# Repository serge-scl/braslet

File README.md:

Here I have collected calculations and drawings of a project for creating a device for removing disposable medical gloves with subsequent storage, accounting and disposal. This procedure is necessary to avoid a significant risk of infection during the work of medical staff. Various visual aids here offer a written and illustrated procedure on how to properly remove a disposable glove to avoid contact with a contaminated surface. However, the human factor suggests that sooner or later a mistake happens. This possibility is exacerbated by the factor of fatigue and stress.
The root directory contains files where I make various calculations. The earliest calculations related to the overall dimensions of the bracelet and its details relative to the size of the coverage of a man's or woman's wrist. These calculations cannot be called accurate. These are just some starting points.
Another group of calculations concerned the ability to determine the forces that a pneumatic mechanism must create for successful operation. This calculation showed that the range can vary quite widely. In the future, using differential equations will allow us to find more optimal values.
And the third type of calculation is the calculation of the solenoid valve that controls the operation of the suction cup. I tried to verify these calculations as far as possible.
The designCAD folder contains drawings in an open format. This work has not yet been completed in its entirety. So far, there are no drawings of the case, the upper and lower parts of the entire device, and it remains to be done. In the upper part there will be a working niche with a bracelet, and receivers and micropumps working with it. At the bottom there will be a negative pressure fan and storage for used gloves. So far, only part of the drawings of the bracelet have been made. This is a vacuum chamber with a solenoid valve and part of a pneumatic drive. All this is still in the form of separate parts without assembly. In the near future, we plan to complete the vacuum line and pneumatic drive.
Kicad pcb will contain two PCBs in two separate projects. This is a power control unit for the suction cup valve and a sensor unit that registers the correct touch of the hand with the glove. How the PCBs are attached can be seen in the sub_asstmbly/solenoid_in_chamb01 file. The inputs and outputs of these blocks are made in such a way that various types of microcontrollers can be connected. I did not finish the topology of the circuits, since the type of connectors may still be different.

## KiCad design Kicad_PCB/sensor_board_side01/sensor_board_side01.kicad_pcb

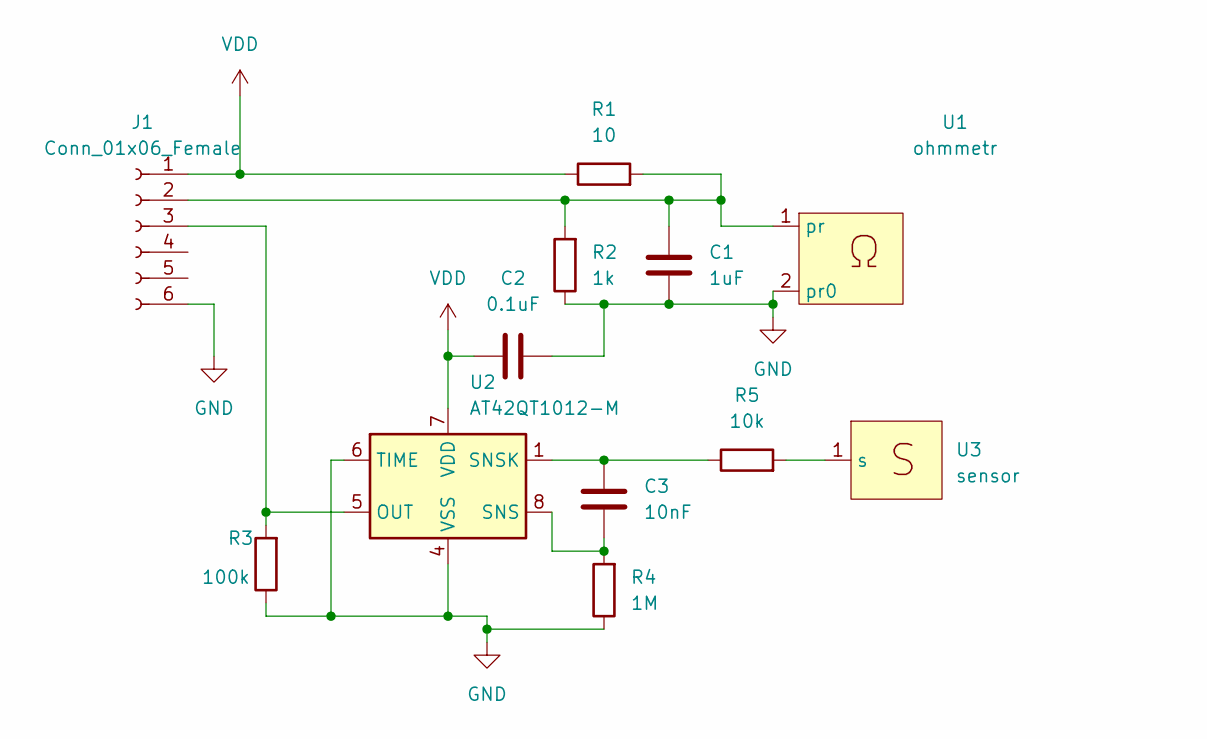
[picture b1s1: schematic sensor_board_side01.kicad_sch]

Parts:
C1: 1uF; C_0805_2012Metric
C2: 0.1uF; C_0805_2012Metric
C3: 10nF; C_0805_2012Metric
J1: Conn_01x06_Female; Hirose_DF13-06P-1.25DSA_1x06_P1.25mm_Vertical
R1: 10; R_0402_1005Metric
R2: 1k; R_0402_1005Metric
R3: 100k; R_0402_1005Metric
R4: 1M; R_0402_1005Metric
R5: 10k; R_0402_1005Metric
U1: ohmmetr; ohm_metr
U2: AT42QT1012-M; DFN-8-1EP_2x2mm_P0.5mm_EP0.9x1.5mm
U3: sensor; toch_sens

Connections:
GND: C1.2, C2.2, J1.6, R2.1, R3.1, R4.1, U1.2 (pr0), U2.4 (VSS), U2.6 (TIME), U2.9 (VSS)
unnamed: C1.1, J1.2, R1.2, R2.2, U1.1 (pr)
unnamed: C3.1, R4.2, U2.8 (SNS)
unnamed: C3.2, R5.1, U2.1 (SNSK)
unnamed: J1.3, R3.2, U2.5 (OUT)
unnamed: R5.2, U3.1 (s)
VDD: C2.1, J1.1, R1.1, U2.7 (VDD)

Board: 2 copper layers, 12 parts (1 on the bottom side), 7 nets, no tracks yet.

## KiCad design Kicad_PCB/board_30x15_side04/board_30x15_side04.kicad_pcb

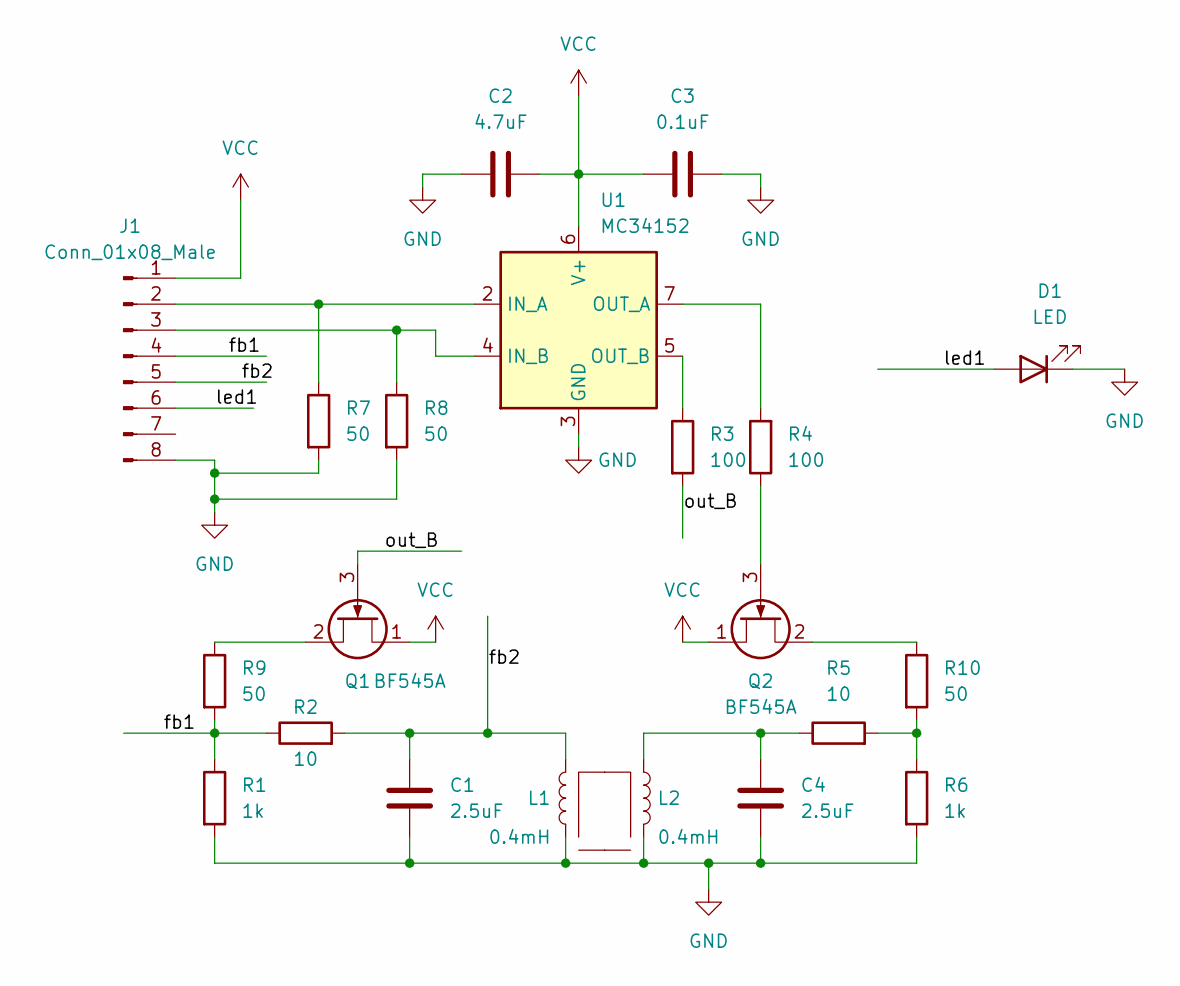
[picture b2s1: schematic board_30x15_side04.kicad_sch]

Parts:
C1, C4: 2.5uF; C_0805_2012Metric
C2: 4.7uF; C_0805_2012Metric
C3: 0.1uF; C_0805_2012Metric
D1: LED; LED_D1.8mm_W1.8mm_H2.4mm_Horizontal_O1.27mm_Z1.6mm
J1: Conn_01x08_Male; Hirose_DF13-08P-1.25DSA_1x08_P1.25mm_Vertical
L1, L2: 0.4mH; sole_coil
Q1, Q2: BF545A; SOT-23
R1, R6: 1k; R_0402_1005Metric
R2, R5: 10; R_0402_1005Metric
R3, R4: 100; R_0402_1005Metric
R7, R8, R9, R10: 50; R_0402_1005Metric
U1: MC34152; SOIC-8_3.9x4.9mm_P1.27mm

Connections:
/fb1: J1.4, R1.1, R2.1, R9.2
/fb2: C1.1, J1.5, L1.1, R2.2
/led1: D1.2 (A), J1.6
/out_B: Q1.3 (G), R3.2
GND: C1.2, C2.1, C3.2, C4.2, D1.1 (K), J1.8, L1.2, L2.2, R1.2, R6.2, R7.2, R8.2, U1.3 (GND)
unnamed: C4.1, L2.1, R5.1
unnamed: J1.2, R7.1, U1.2 (IN_A)
unnamed: J1.3, R8.1, U1.4 (IN_B)
unnamed: Q1.2 (D), R9.1
unnamed: Q2.2 (D), R10.1
unnamed: Q2.3 (G), R4.1
unnamed: R3.1, U1.5 (OUT_B)
unnamed: R4.2, U1.7 (OUT_A)
unnamed: R5.2, R6.1, R10.2
VCC: C2.2, C3.1, J1.1, Q1.1 (S), Q2.1 (S), U1.6 (V+)

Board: 2 copper layers, 21 parts (2 on the bottom side), 15 nets, no tracks yet.

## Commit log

2020-07-20 20.7.20 ferst braslet calk
2020-07-24 24.07/20 trid module calc
2020-07-28 28 07 20 error correct
2020-07-28 28 07 20 error correct 2
2020-08-04 4 08 20 buff tank w
2021-01-07 positive check of the first conditions
2021-06-11 the effort of the electromagnetic
2021-06-12 calculating the resistance of a conductor
2021-06-13 magnet dimensions
2021-06-14 add description
2021-06-15 module2 new calc
2021-06-16 angles of rotation when stretching the bracelet
2021-07-01 calculation of the vacuum chamber and pneumatic actuators
2021-07-13 Create README.md
    Completion of the cycle of preliminary calculations
2021-07-13 back cover with feeder
2021-07-13 cover with plug
2021-07-13 vacuum transfer tube - spring
2021-07-13 magnetic valve armature
2021-07-13 rubber valve nipple
2021-07-13 vacuum chamber floor
2021-07-13 suction cup
2021-07-13 vacuum chamber shell
    assembly with coil contacts and pneumatic line
2021-07-13 magnetic coil
2021-07-13 magnetic core
2021-07-13 assembly floor and suction cup
2021-07-13 magnetic coil contact
2021-07-13 direct air line
2021-07-13 assembly of pneumatic actuator
2021-07-13 bottom of the pneumatic actuator
2021-07-13 top of the pneumatic actuator
2021-07-13 actuator part
2021-07-13 actuator connection
2021-07-17 feeder tap pressure air
2021-07-17 air line with feeder inlet
2021-07-17 assembly of the chamber 2
    assembly of the shell of the vacuum chamber with a feeder
2021-07-18 top fastener
2021-07-18 min dim feeder
2021-07-18 min dim fd chamb
2021-07-19 suspension assembly
2021-07-30 PCB create
2021-07-30 pcb board open
2021-07-30 coil and all
2021-07-31 cap toch sensor
2021-07-31 sensor Vlt
2021-08-07 logic remake
2021-08-29 kicad correct in now git
2022-01-04 new file ac current for solenoid
2022-01-24 optimize the whole device
2022-01-25 the module2 is fixable, pneumAct and slid_pneum to junk code
2022-01-28 gas flow equation
2022-01-30 calculation correction
2022-01-31 pneumatic actuator ring, module2 comment out
2022-02-03 vacuum tube spring effect
2022-02-04 vacuum chamber
2022-02-06 suction cup ratio
2022-02-09 vacuum valve spring
2022-02-10 valve spring CAD drawing
2022-02-14 solenoid calculation error fix
2022-02-16 solenoid inductance
2022-02-18 Capacitor and operating frequency.
2022-02-19 calcsegments is dried, valve_forceAC 4 kHz
2022-02-20 new magnet core
2022-02-21 gitignr
2022-02-21 del .pyc
2022-02-21 gitignor2
2022-02-22 new magnet coil sizes
2022-02-24 new dimensions vacuum chamber
2022-02-25 platform for magnet
2022-02-26 spring stop washer
2022-02-27 pin for spring
2022-02-28 cross valve
2022-03-01 new vacuum chamber floor
2022-03-03 new suction cup
2022-03-04 vacuum line throttle
2022-03-06 valve slider
2022-03-08 three-section actuator 9 mm
2022-03-10 side part of the actuator
2022-03-14 soft pneumatic pistons
2022-03-15 screw
2022-03-22 ellipse shape vacuum tube
2022-03-25 Readme
2022-03-30 Frame spring
2022-04-01 wacuum pip new
2022-04-06 branch pipe tee vacuum
2022-04-07 frame spring adjustment
2022-04-10 frame spring upgrade middle fix
2022-04-13 shell chamb 12 add brackets
2022-04-17 pip air press
2022-04-18 pip for air pressure 4x4
2022-04-19 adapter actuators
2022-04-20 magnet coil 70 wire
2022-04-21 feeder press air
2022-04-24 vacuum line connect
2022-04-24 shell chamb 12 error
2022-04-25 assembly for drilling fasteners
2022-04-26 assemble: solenoid, coil and chamber
2022-04-27 valve, suction cup, floor and spring
2022-04-28 valve 14 mm ln
2022-04-30 ring vacuum line
2022-05-03 ring pneumatic actuator
2022-05-09 PCB foot and connect
2022-05-10 3 coil pins and ground
2022-05-10 pins and ground 2 correct
2022-05-16 new PCB
2022-05-23 components schema
2022-05-28 sensor board
2022-05-29 sensor board 2
2022-05-29 sensors board 3 try
2022-05-31 ohmmeter circuit
2022-06-04 Sensor Board Schematic
2022-06-04 schematic and footprint libraries
2022-06-07 waste intake face slot and air receivers
2022-06-11 bracelet motion min max
2022-06-25 bracelet weight
2022-06-27 working pressure during expansion
2022-07-04 spring suspension
2022-07-05 spring suspension pls cad
2022-07-08 top loading module shell
2022-07-11 inner wrapper with holes
2022-07-13 sensor move
2022-07-15 conic spring in sockets with PCB
2022-07-16 spring module bottom cover
2022-07-19 lips
2022-07-22 cover module shell ass
2022-07-24 cover module shell assm 2 top
2022-07-28 solenoid with coils and pin
2022-08-02 pip feeders ring cluster
2022-08-05 pip feeders cluster 3 mm
2022-08-11 valve logic
2022-08-26 verification of calculations by duplication
2022-08-31 spring work equation
2022-09-03 differential equation with data
2022-09-10 new computer and pause
2022-09-22 test new computer
2022-10-13 Raspberry Pi Pico cad
2022-10-20 Raspberry Pi Pico cad fix to asm
2022-10-22 Raspberry Pi Pico 3 pcb add
2022-11-01 valve logic 2 physical level
2022-11-08 ADC valve simulator
2022-11-11 sampling to ADC 100 kHz
2022-11-14 short coil for captcha
2022-11-19 microcontroller
2022-11-23 microcontroller and gitignore
2022-11-24 new idea of cup with tongue
2022-11-26 tongue in sub assembly
2022-11-30 new spring diametric
2022-12-12 new design of vacuum chamber
2022-12-16 updating the vacuum chamber in assemblies
